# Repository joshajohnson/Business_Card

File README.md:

# Business_Card
Blinky Business Card using a PIC12 and some LED's

Work in progress.
Current plan is to count from 0 to 255 in binary, and allow for single stepping and clocked counting, with variable frequency for the clock.

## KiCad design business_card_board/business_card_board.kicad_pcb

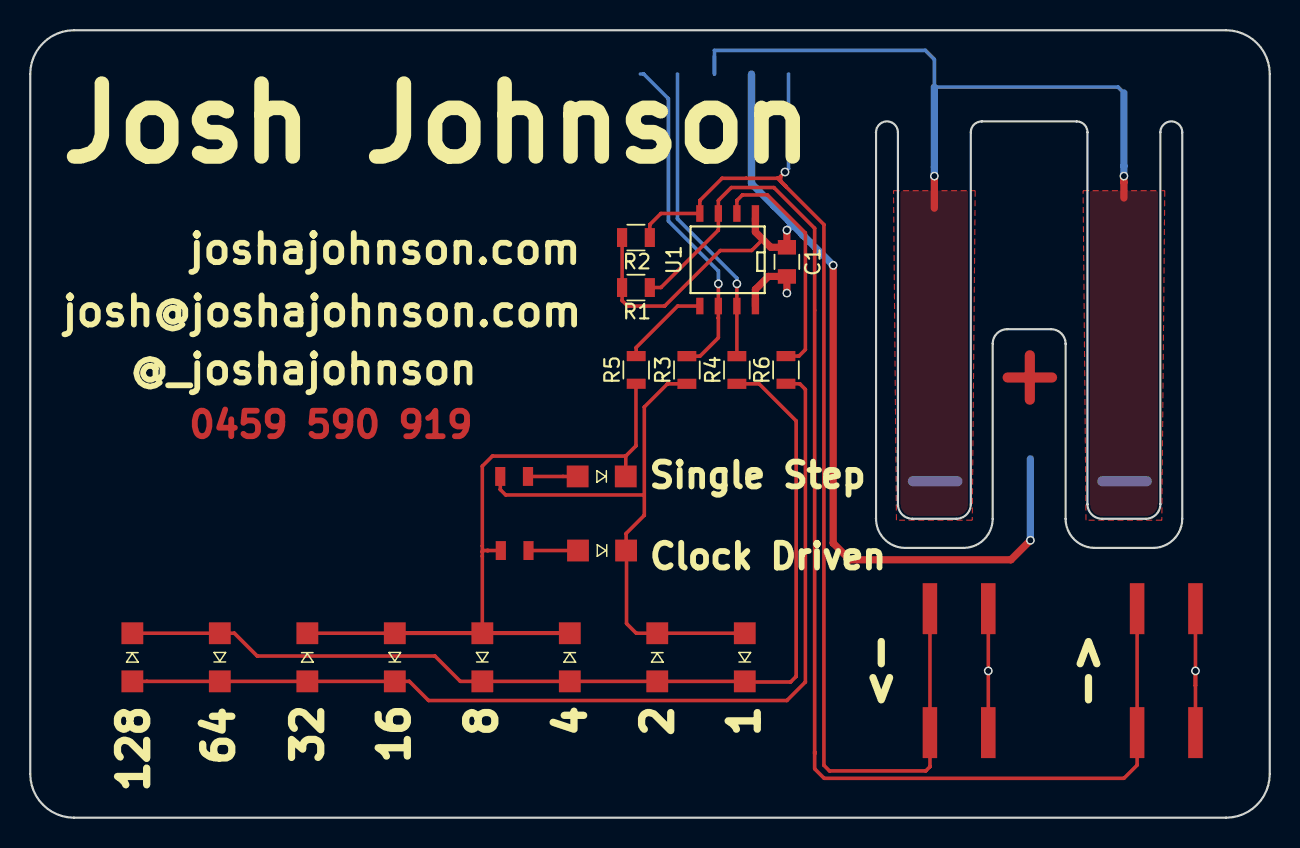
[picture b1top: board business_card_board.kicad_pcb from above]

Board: 2 copper layers, 85.0 x 54.0 mm, 19 parts (1 on the bottom side), 12 nets.

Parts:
1, 2, 4, 8, 16, 32, 64, 128: LED; LED_1206_NO_REFDES
->: SW_Push; KSEK43GLFS_NoREFDES
<-: SW_Push; KSEK43GLFS_NoREFDES
C1: 0.1u; C_0805
J1: PICKit3_Programmer; Pin_Header_Straight_1x06_Pitch2.54mm_SMD
R1, R2: 10k; R_0805
R3, R4, R5, R6: 65R; R_0805
U1: PIC12F1822; SOIC-8-N

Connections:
GND: ->.1, <-.1, C1.2, J1.3, U1.8
ICSPCLK: J1.5, R3.2, U1.6
ICSPDAT: J1.4, R4.2, U1.7
unnamed: 1.1, 2.2, 4.2, 8.1, 64.2, 128.1, R4.1
unnamed: 1.2, 2.1, R3.1
unnamed: 4.1, 8.2, 16.2, 32.1, R5.1
unnamed: 16.1, 32.2, 64.1, 128.2, R6.1
unnamed: ->.2, R1.2, U1.3
unnamed: R5.2, U1.5
RA5: R6.2, U1.2
VCC: C1.1, J1.2, R1.1, R2.1, U1.1
VPP/~MCLR: <-.2, J1.1, R2.2, U1.4

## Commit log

2018-06-22 Init - buttons toggle LED's
2018-06-22 LED's charlieplexed and working
2018-06-22 Add readme
2018-06-22 schematic captured, footprints associated
2018-06-22 schematic captured, footprints made
2018-06-23 layout almost done
2018-06-24 CR2032 Holder added + everything connected
2018-06-25 minor routing changes + test bit output code
2018-06-26 gerbers sent to fab, small change to trace on d1 after files sent.
2018-07-02 small trace change on right button
2018-07-02 got it counting with buttons + delay
2018-07-02 binary displaying with delay
2018-07-02 interrupt driven flashing
2018-07-03 driven and single step both work at same time
2018-07-04 firmware at v1.0, appears to function as desired
2018-07-05 small changes to decrease ghosting
2018-07-06 board now at v1.1, improved mechanical layout + small routing changes
2018-07-06 more routing improvements
2018-07-06 more routing changes
2018-07-09 v1.1 gerbers finalised
2019-03-17 added schematic as pdf
